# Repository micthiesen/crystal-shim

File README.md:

# Crystal Shim

A water-level interlock for an OASE CrystalSkim 350. An active sensor outside the
aquarium glass reports to an ESP32-C6; a separate mains board filters and switches
the skimmer. The controller and mains board share an enclosure with physical separation.

It runs on configurable 15-minute schedules when the water level permits, with
bounded HomeKit overrides. Every run ends automatically. See [behavior](docs/controls.md).
Pushover alerts report confirmed water-level transitions in either direction.
An ESP-hosted local webpage implements settings and schedules. The sensor
targets a freshwater tank with 5 mm glass. Its slim board adheres below the rim
with thin mounting film and a left-exiting pigtail.

**Build approach:** one complete design and fabrication cycle for all three
final-use boards. Complete design reviews before fabrication, then calibrate and
commission the assembled unit. No separate prototype phase is planned.

**Status:** the compact three-board designs are prepared for owner routing.
See [current state](docs/STATE.md) for current checks and accepted handoff receipts.
The C6 application includes sensing, relay/watchdog control, retained state,
private Matter provisioning, local settings and verified-TLS Pushover delivery.
The present hardware includes fixed 12 V power, three future pump drivers and a
second sensor port under the [refill attachment contract](docs/design/refill-expansion.md).
Future refill/conditioning behavior is deferred. Routing, fabrication release and
physical calibration/commissioning remain separate work.

Start with [the overview](docs/overview.md) and [current state](docs/STATE.md).
The [decision register](docs/decisions.md) tracks open inputs and release gates.

- [Design dossier](docs/README.md)
- [Firmware and simulator](firmware/README.md)
- [PCB tooling and three board areas](pcb/README.md)
- [Bill of materials](bom/README.md)
- [Commissioning matrix](testing/README.md)
- [Build sequence](docs/build.md)

Use the pinned toolchains described in the firmware and PCB READMEs. Then:

```sh
cd pcb
bun install --frozen-lockfile
cd ..
sh scripts/check.sh
python3 .agents/skills/sync/sync-status.py
```

Based on `../stillair`: Rust host core + CLI + separate ESP32-C6 app, Bun/tscircuit
authoring, and KiCad downstream production tooling. Relevant skills and tools have
a reciprocal sync map; Stillair's board designs and fan behavior are not imported.

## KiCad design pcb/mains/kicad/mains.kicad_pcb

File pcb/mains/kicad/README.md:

# Power-board routing handoff

Open [mains.kicad_pro](mains.kicad_pro). The accepted **150 × 110 mm, two-layer**
lower board has 26 footprints and **31 unrouted connections**. Strict ERC,
schematic parity and ordinary DRC pass. Four 3.2 mm NPTH mounts are inset 7 mm
and align with the controller, with 45 mm clear board-face separation.

J1–J4 use Phoenix 1868076 two-position side-entry screw terminals, with both positions used. All 106 previous owner-routed
tracks were cleared as authorized. Eleven ground vias, isolated F.Cu/B.Cu pours,
mounting/barrier exclusions, netclasses and bounded pad-escape rules are applied.
The saved two-layer stack totals 1.6 mm.

Follow the [routing guide](../../../docs/design/routing-guardrails.md). Keep the
primary/SELV boundary intact. Native DRC enforces 3.2 mm between different primary
nets and 8 mm primary-to-SELV clearance. Use netclass width with connected-track
inheritance disabled; narrow segments belong only inside their named pad escapes.

[Stacked-layout evidence](evidence/stacked-layout/) includes the accepted ECO,
exact pad/field parity, strict ERC, filled DRC and five native rule probes.
[Connector ECO](../../../docs/design/evidence/connector-eco/mains/) replaces the headers and obsolete NC labels.
[Final preparation](evidence/final-preparation/) adds service labels and verifies
mask/paste/slot geometry. [The handoff lock](../design/handoff.lock.json) binds
current acceptance. Older
evidence describes superseded board dimensions and connector orientations.

Keep this project, board, custom rules and local libraries together. Route,
refill with **B**, save and run `sh scripts/check-routing.sh mains --final`
before fabrication checks/export. Unconnected items are allowed without `--final`.

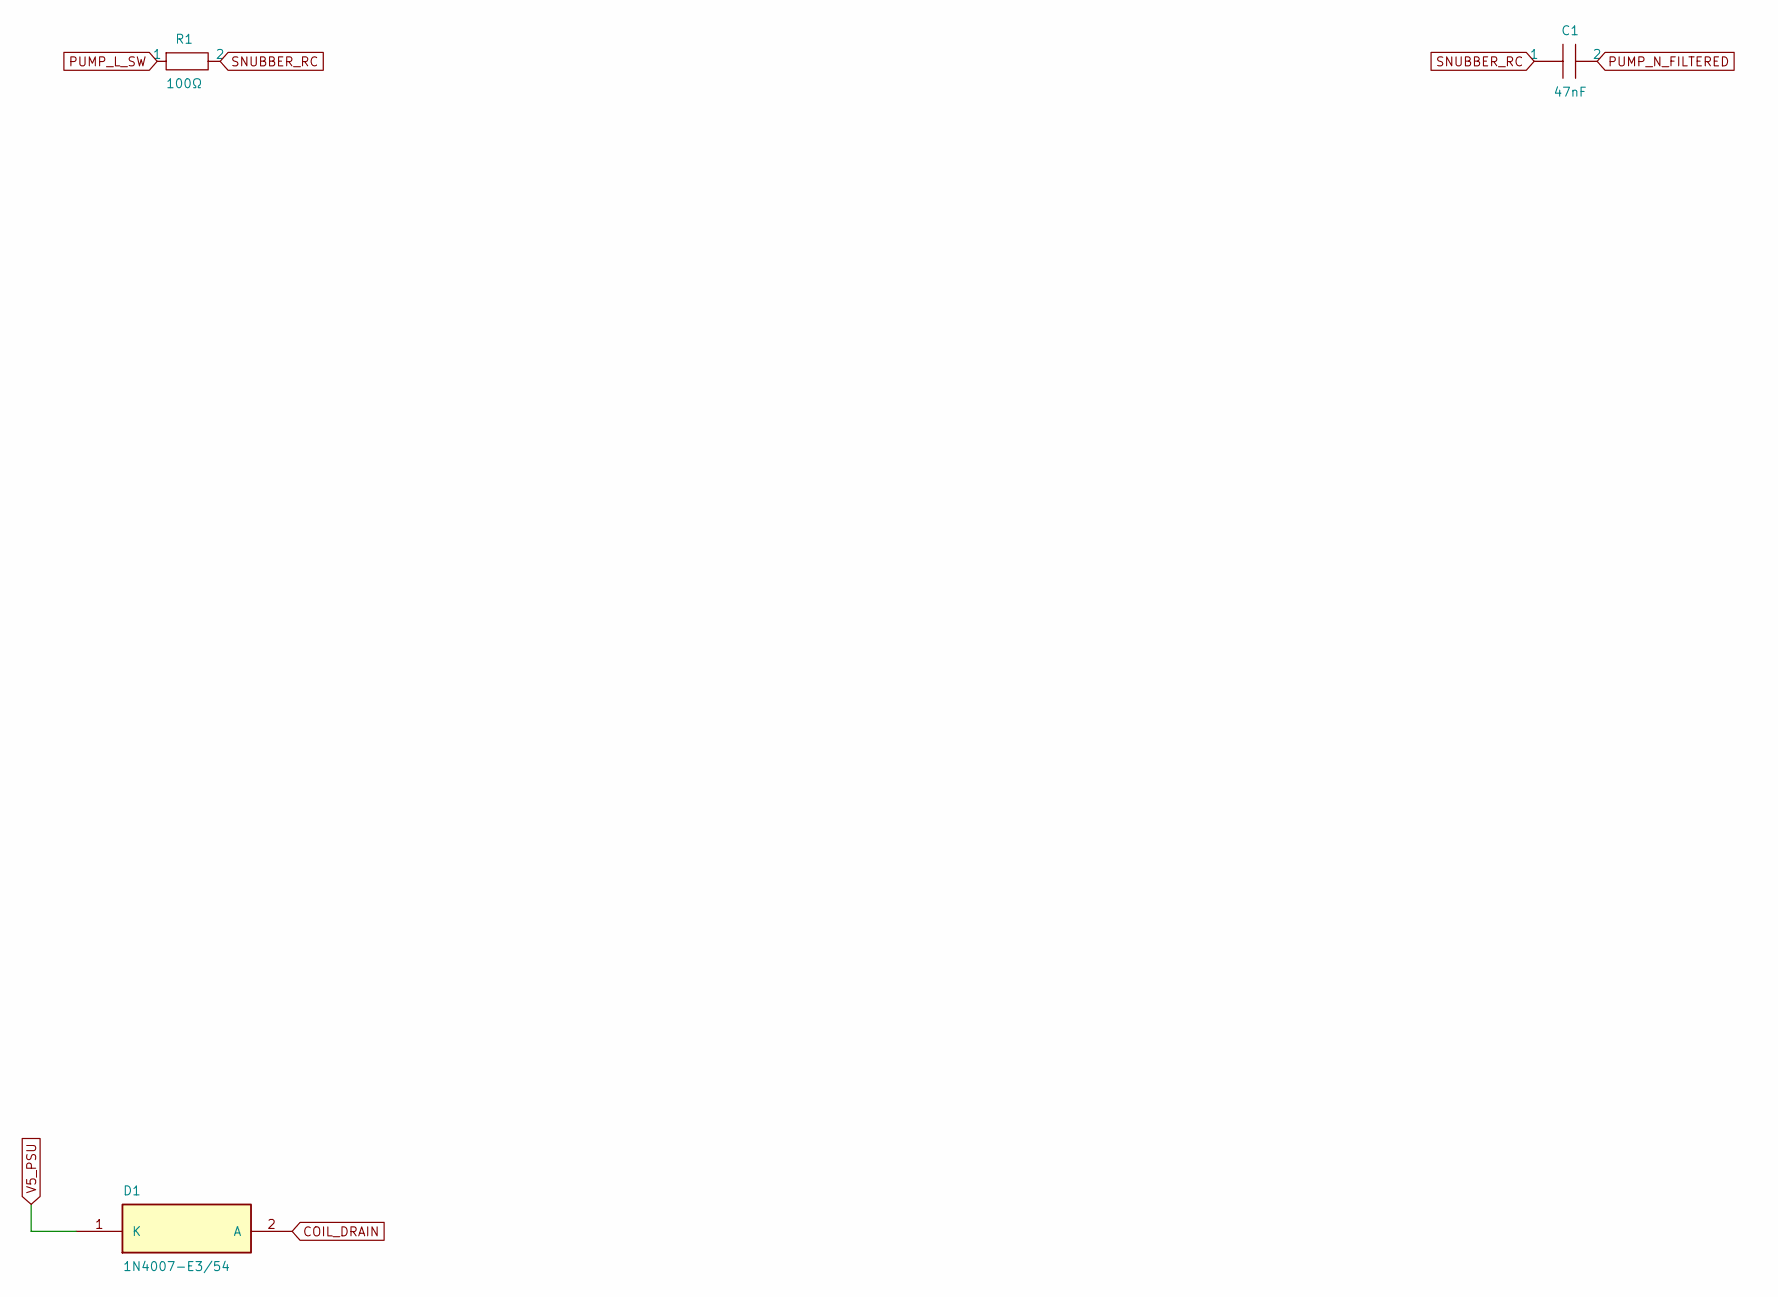
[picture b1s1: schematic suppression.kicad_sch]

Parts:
C1: 47nF; Mains_C1; MPN B32921C3473K000
D1: 1N4007-E3/54; Mains_D1; MPN 1N4007-E3/54
R1: 100Ω; Mains_R1; MPN PR02FS0201000KA100

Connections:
COIL_DRAIN: D1.2 (A); also elsewhere on the board
PUMP_L_SW: R1.1; also elsewhere on the board
PUMP_N_FILTERED: C1.2; also elsewhere on the board
SNUBBER_RC: C1.1, R1.2
V5_PSU: D1.1 (K); also elsewhere on the board

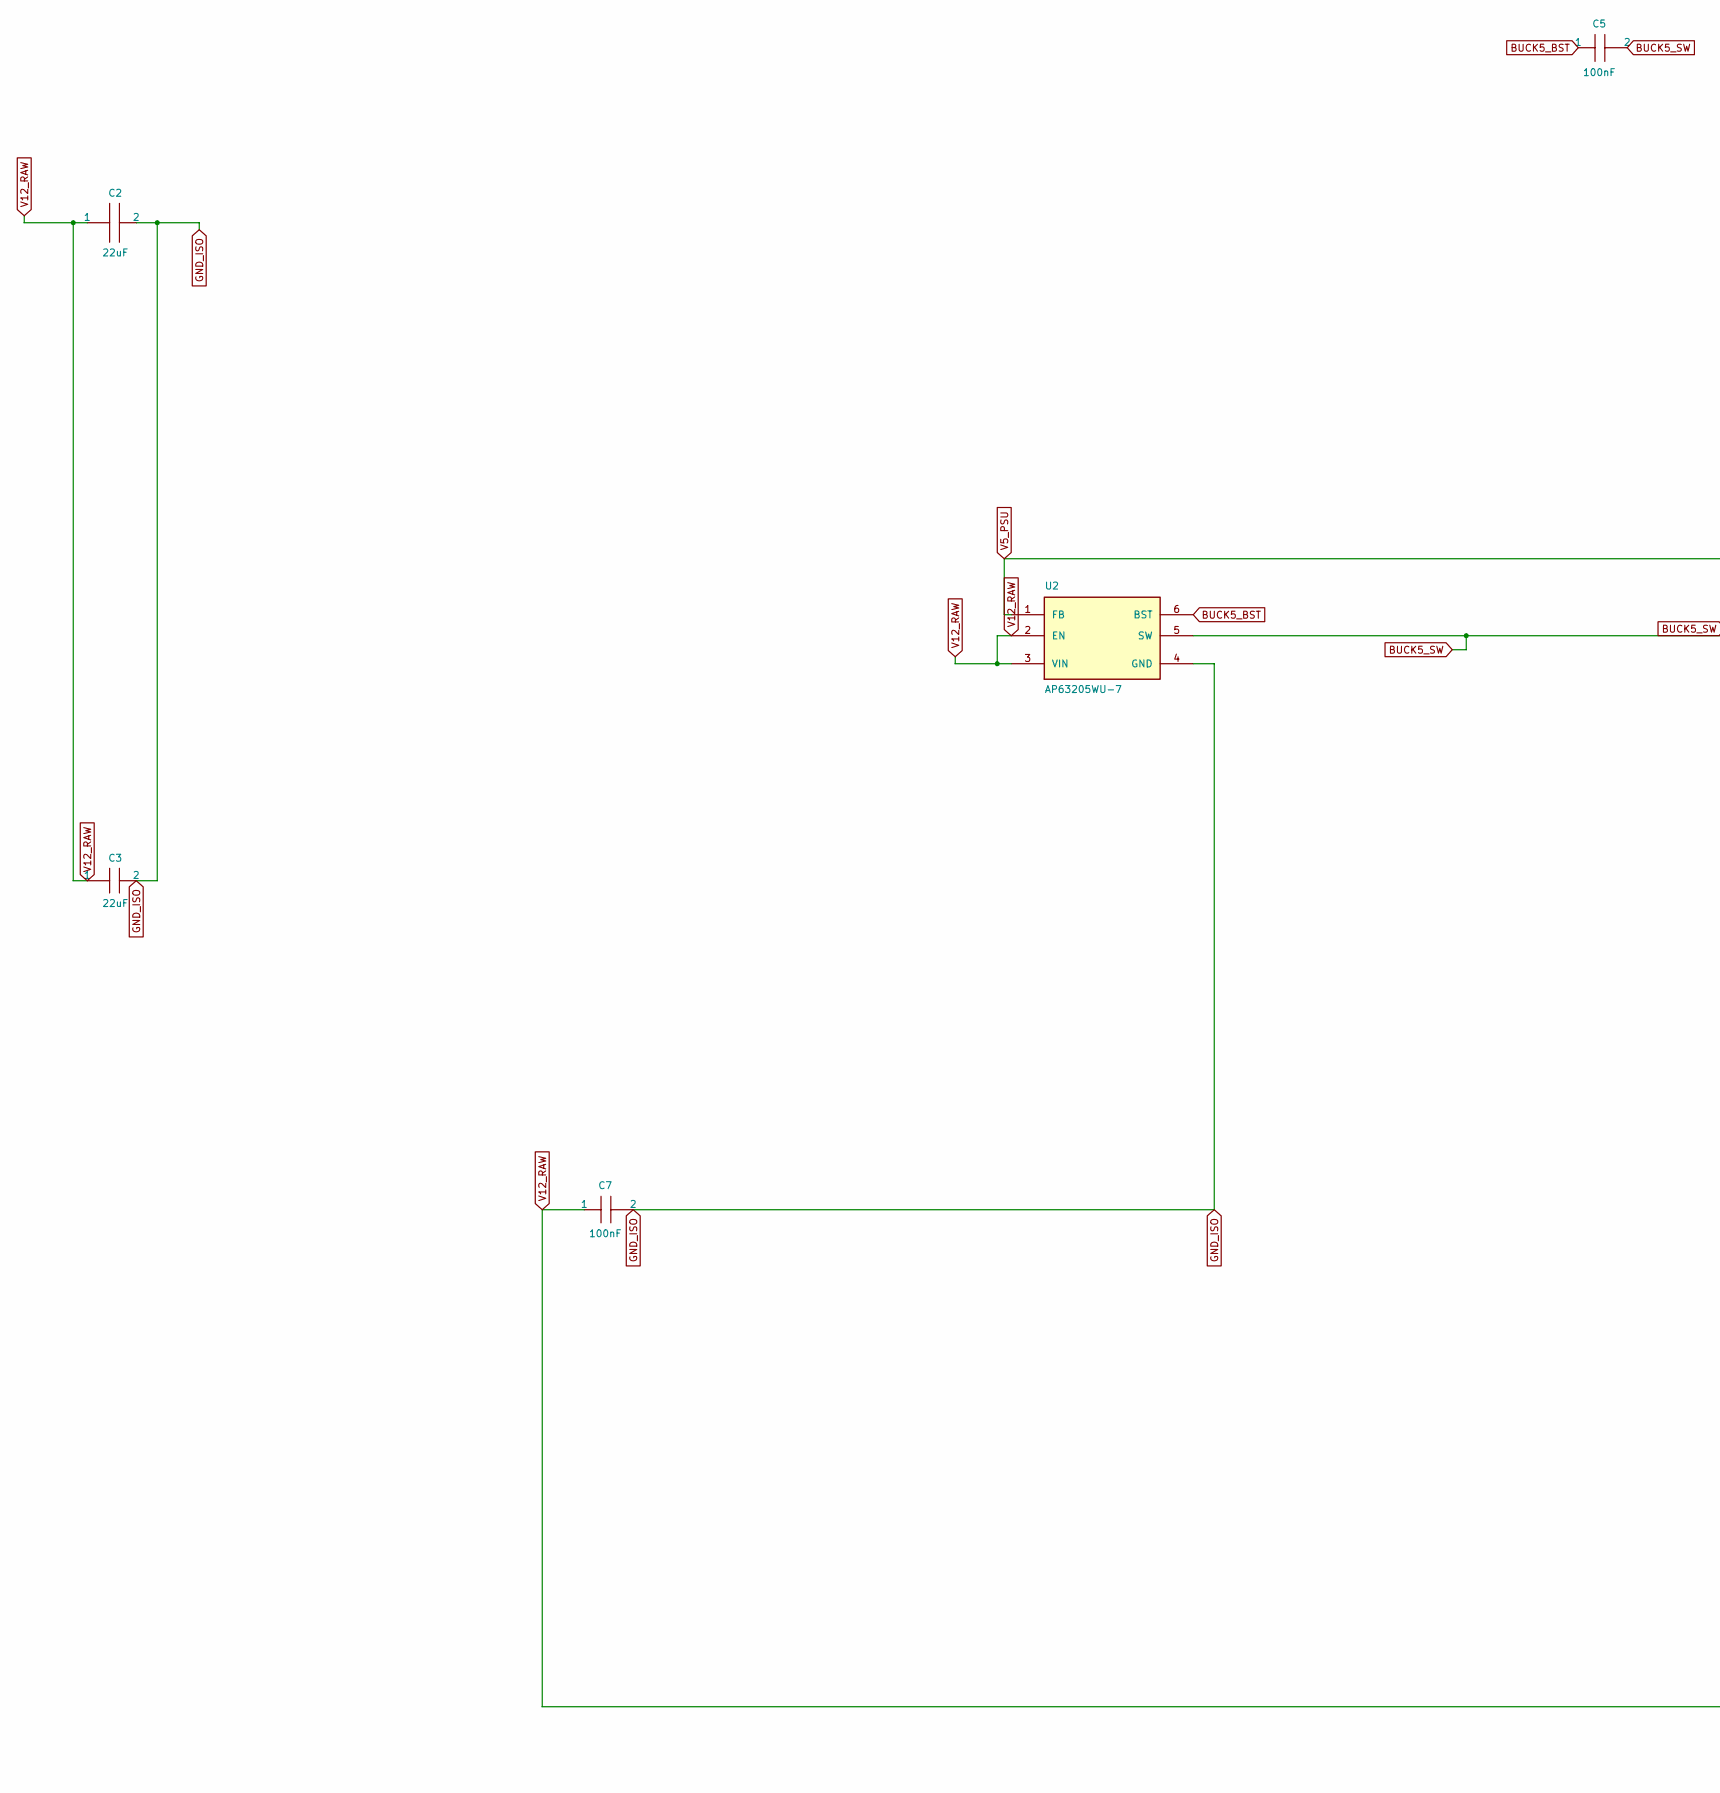
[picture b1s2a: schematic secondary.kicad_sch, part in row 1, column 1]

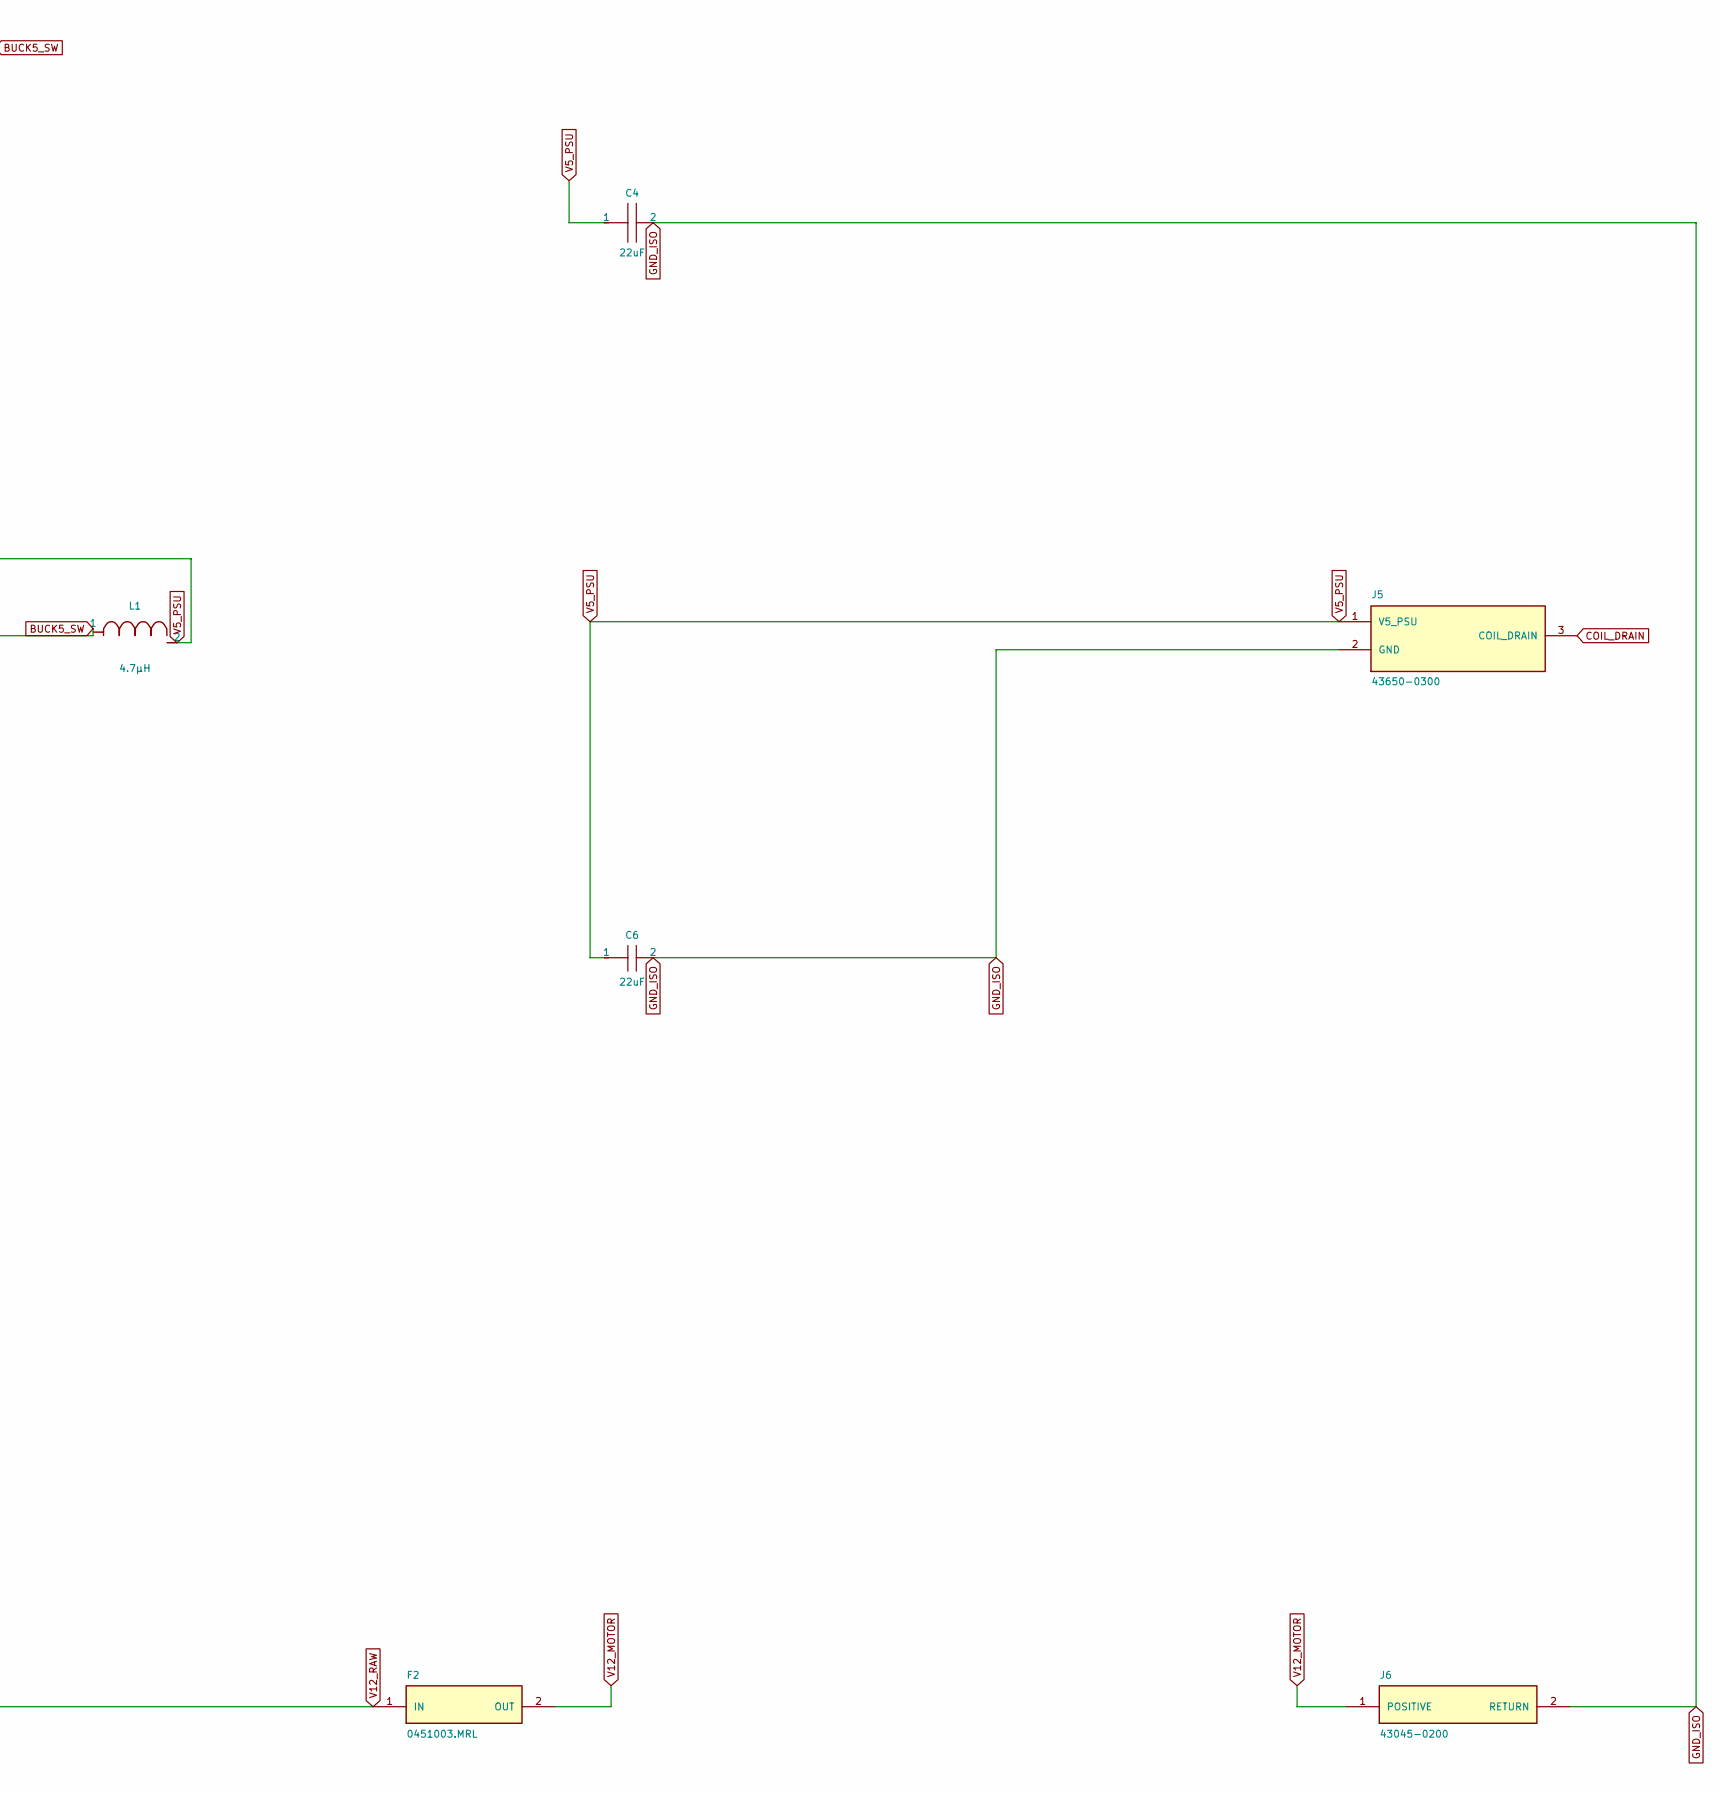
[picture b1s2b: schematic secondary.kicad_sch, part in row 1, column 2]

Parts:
C2: 22uF; Mains_C2; MPN GRM32ER71E226ME15L
C3: 22uF; Mains_C3; MPN GRM32ER71E226ME15L
C4: 22uF; Mains_C4; MPN GRM32ER71E226ME15L
C5: 100nF; Mains_C5; MPN C1608X7R1H104K080AA
C6: 22uF; Mains_C6; MPN GRM32ER71E226ME15L
C7: 100nF; Mains_C7; MPN C1608X7R1H104K080AA
F2: 0451003.MRL; Mains_F2; MPN 0451003.MRL
J5: 43650-0300; Mains_J5; MPN 43650-0300
J6: 43045-0200; Mains_J6; MPN 43045-0200
L1: 4.7µH; Mains_L1; MPN SRP5030TA-4R7M
U2: AP63205WU-7; Mains_U2; MPN AP63205WU-7

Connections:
BUCK5_BST: C5.1, U2.6 (BST)
BUCK5_SW: C5.2, L1.1, U2.5 (SW)
COIL_DRAIN: J5.3 (COIL_DRAIN); also elsewhere on the board
GND_ISO: C2.2, C3.2, C4.2, C6.2, C7.2, J5.2 (GND), J6.2 (RETURN), U2.4 (GND); also elsewhere on the board
V5_PSU: C4.1, C6.1, J5.1 (V5_PSU), L1.2, U2.1 (FB); also elsewhere on the board
V12_MOTOR: F2.2 (OUT), J6.1 (POSITIVE)
V12_RAW: C2.1, C3.1, C7.1, F2.1 (IN), U2.2 (EN), U2.3 (VIN); also elsewhere on the board

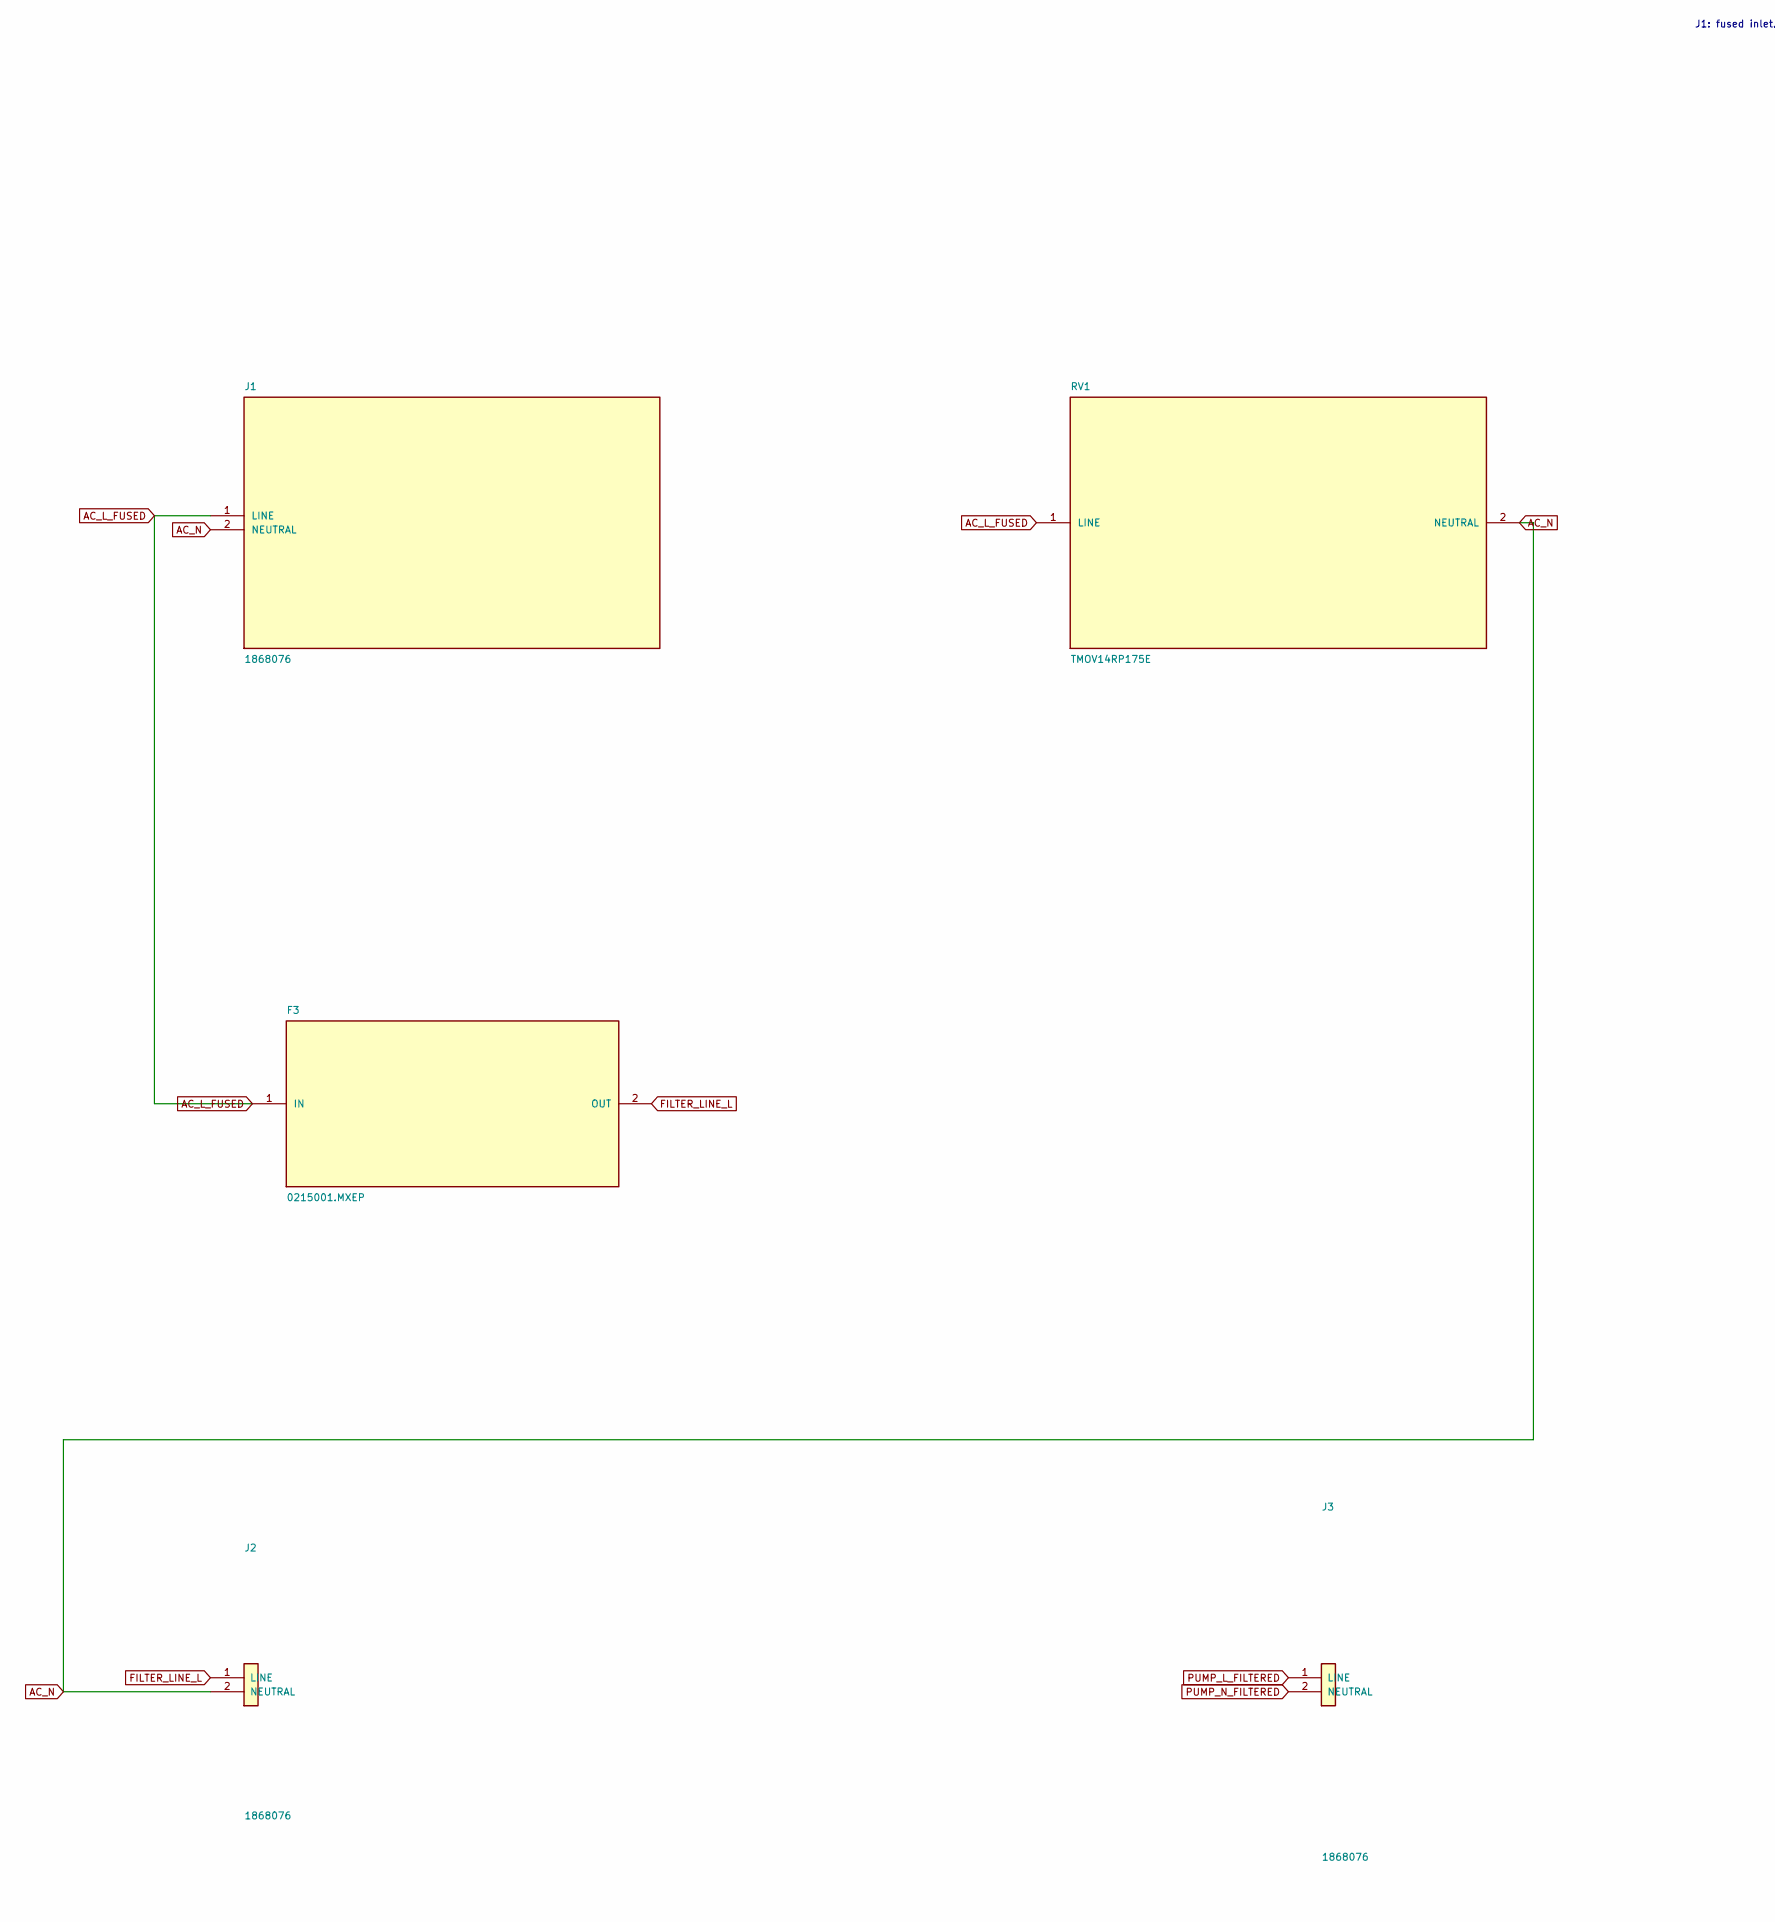
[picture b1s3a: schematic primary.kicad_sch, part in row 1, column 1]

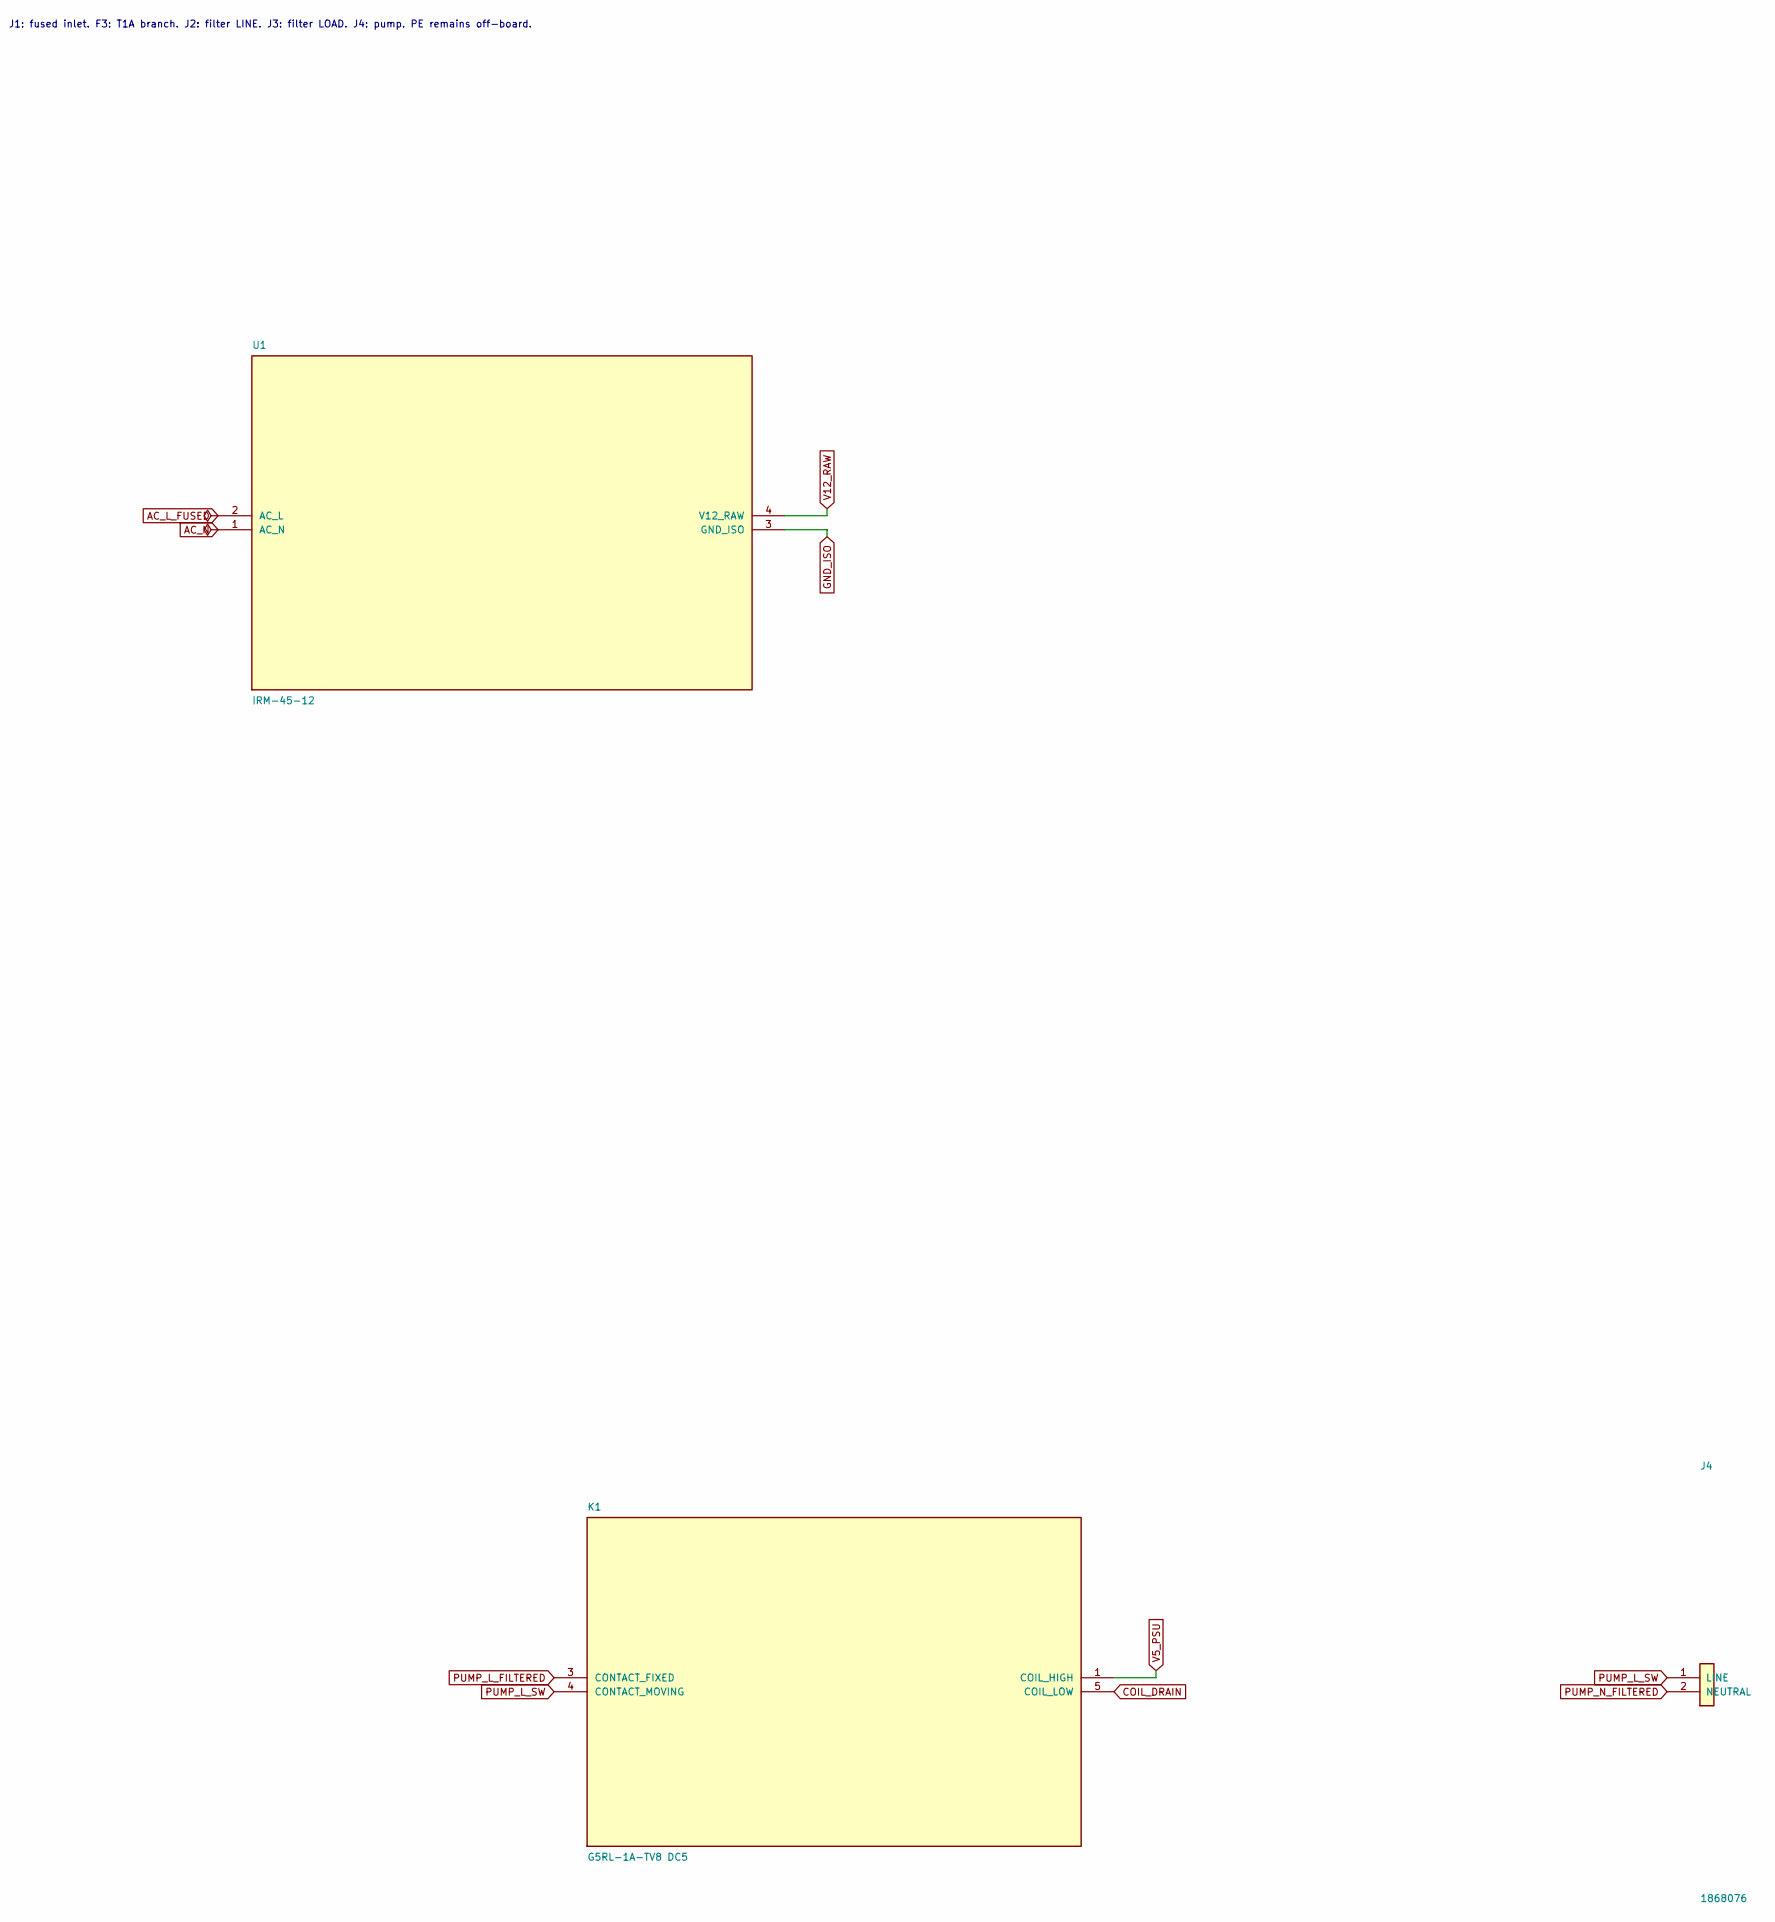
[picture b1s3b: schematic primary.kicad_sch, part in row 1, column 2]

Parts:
F3: 0215001.MXEP; Mains_F3; MPN 0215001.MXEP
J1: 1868076; Mains_J1; MPN 1868076
J2: 1868076; Mains_J2; MPN 1868076
J3: 1868076; Mains_J3; MPN 1868076
J4: 1868076; Mains_J4; MPN 1868076
K1: G5RL-1A-TV8 DC5; Mains_K1; MPN G5RL-1A-TV8 DC5
RV1: TMOV14RP175E; Mains_RV1; MPN TMOV14RP175E
U1: IRM-45-12; Mains_U1; MPN IRM-45-12

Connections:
AC_L_FUSED: F3.1 (IN), J1.1 (LINE), RV1.1 (LINE), U1.2 (AC_L)
AC_N: J1.2 (NEUTRAL), J2.2 (NEUTRAL), RV1.2 (NEUTRAL), U1.1 (AC_N)
COIL_DRAIN: K1.5 (COIL_LOW); also elsewhere on the board
FILTER_LINE_L: F3.2 (OUT), J2.1 (LINE)
GND_ISO: U1.3 (GND_ISO); also elsewhere on the board
PUMP_L_FILTERED: J3.1 (LINE), K1.3 (CONTACT_FIXED)
PUMP_L_SW: J4.1 (LINE), K1.4 (CONTACT_MOVING); also elsewhere on the board
PUMP_N_FILTERED: J3.2 (NEUTRAL), J4.2 (NEUTRAL); also elsewhere on the board
V5_PSU: K1.1 (COIL_HIGH); also elsewhere on the board
V12_RAW: U1.4 (V12_RAW); also elsewhere on the board

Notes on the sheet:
J1: fused inlet. F3: T1A branch. J2: filter LINE. J3: filter LOAD. J4: pump. PE remains off-board.

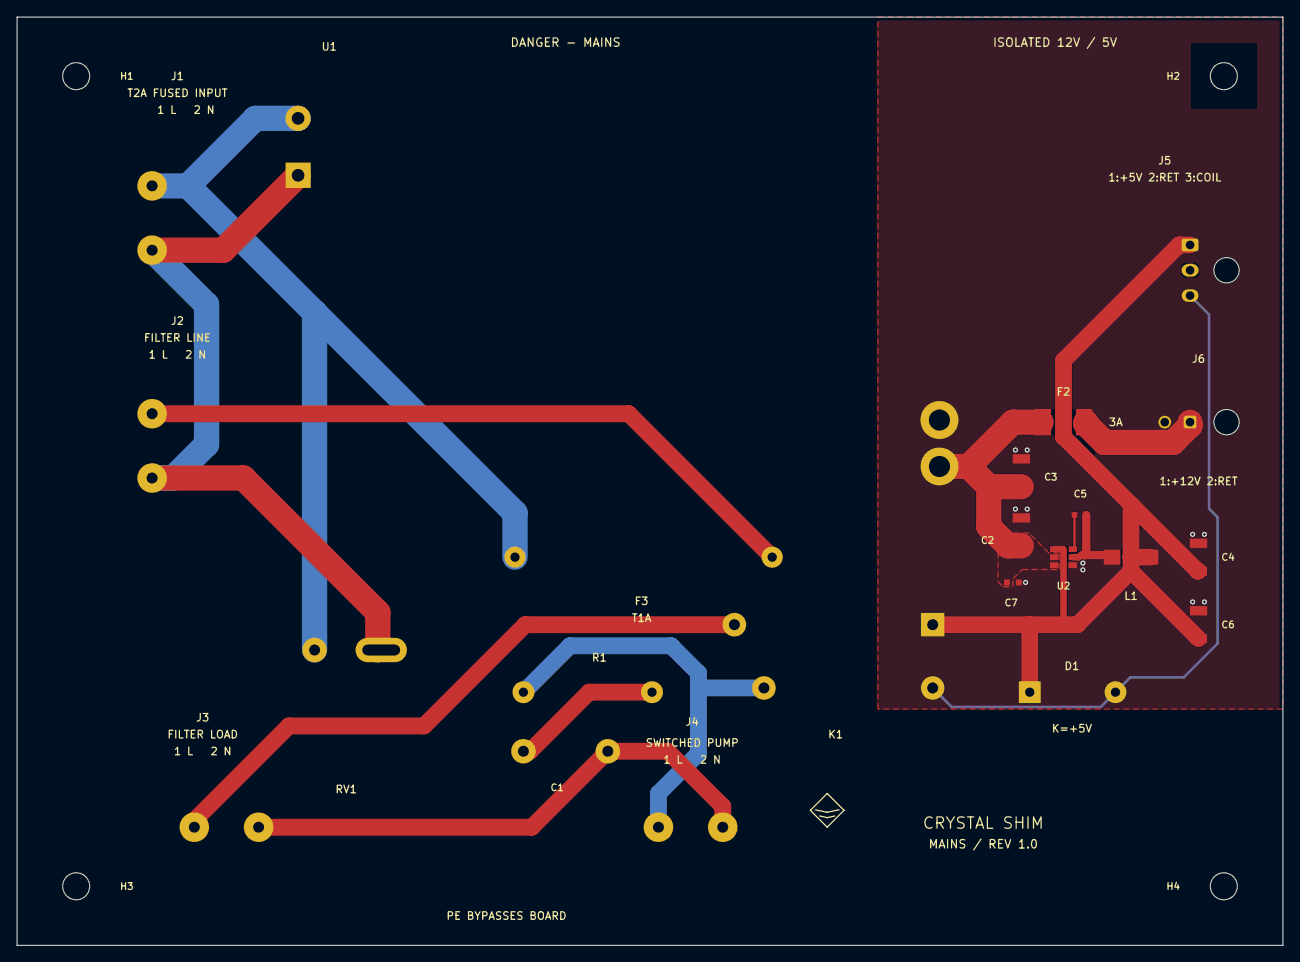
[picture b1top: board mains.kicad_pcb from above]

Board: 2 copper layers, 150.0 x 110.0 mm, 26 parts (0 on the bottom side), 14 nets.

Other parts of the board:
H1: 3.2mm NPTH; Mains_H1
H2: 3.2mm NPTH; Mains_H2
H3: 3.2mm NPTH; Mains_H3
H4: 3.2mm NPTH; Mains_H4
